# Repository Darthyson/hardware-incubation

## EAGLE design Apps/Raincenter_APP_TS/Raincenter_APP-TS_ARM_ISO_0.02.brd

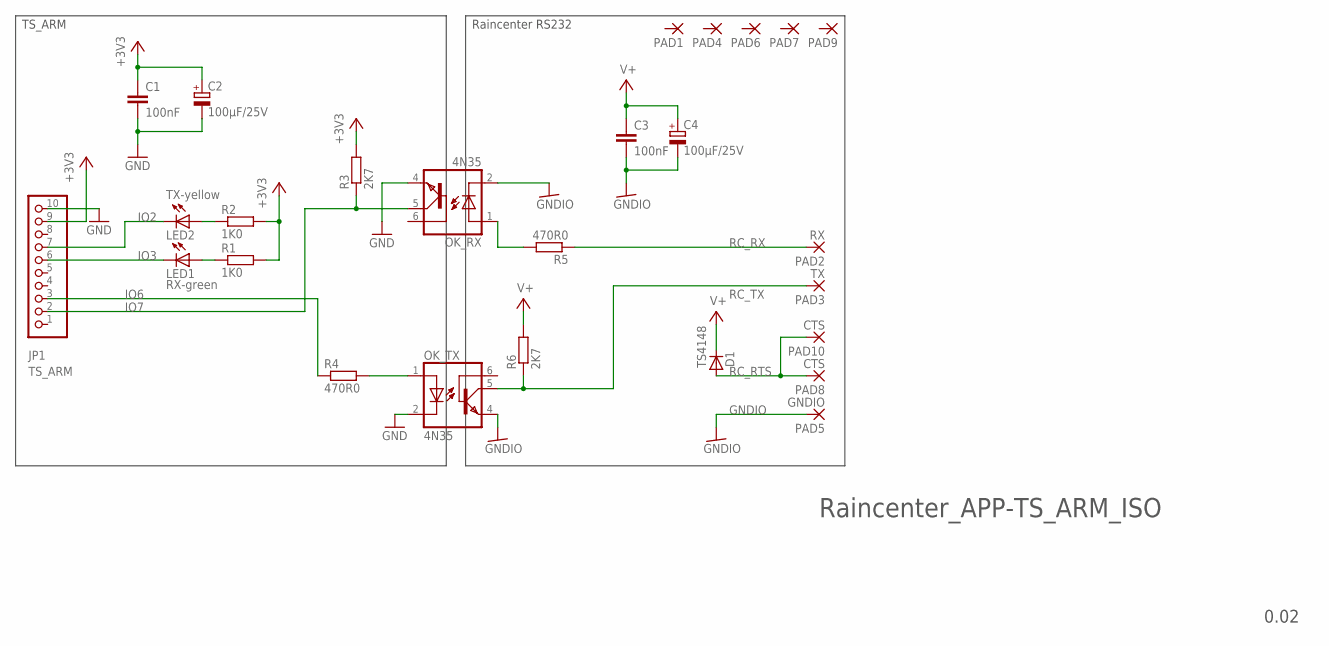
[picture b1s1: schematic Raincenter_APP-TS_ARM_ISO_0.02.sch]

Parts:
C1, C3: 100nF; C1206K
C2, C4: 100µF/25V; PANASONIC_D
D1: TS4148; 1206
JP1: TS_ARM; 1X10
LED1: RX-green; CHIPLED_1206
LED2: TX-yellow; CHIPLED_1206
OK_RX: 4N35; DIL06
OK_TX: 4N35; DIL06
PAD1, PAD4, PAD6, PAD7, PAD9: WIREPADSMD1,27-254; SMD1,27-2,54
PAD2: RX; SMD1,27-2,54
PAD3: TX; SMD1,27-2,54
PAD5: GNDIO; SMD1,27-2,54
PAD8, PAD10: CTS; SMD1,27-2,54
R1, R2: 1K0; R1206
R3, R6: 2K7; R1206
R4, R5: 470R0; R1206

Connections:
+3V3: C1.1, C2.+, JP1.9, R1.2, R2.2, R3.2
GND: C1.2, C2.-, JP1.10, OK_RX.4 (EMI), OK_TX.2 (C)
GNDIO: C3.2, C4.-, OK_RX.2 (C), OK_TX.4 (EMI), PAD5.1
IO2: JP1.7, LED2.C
IO3: JP1.6, LED1.C
IO6: JP1.3, R4.1
IO7: JP1.2, OK_RX.5 (COL), R3.1
unnamed: LED2.A, R2.1
unnamed: OK_RX.1 (A), R5.2
unnamed: OK_TX.1 (A), R4.2
unnamed: LED1.A, R1.1
RC_RTS: D1.ANODE (A), PAD8.1, PAD10.1
RC_RX: PAD2.1, R5.1
RC_TX: OK_TX.5 (COL), PAD3.1, R6.1
V+: C3.1, C4.+, D1.KATHODE (K), R6.2

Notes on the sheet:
Raincenter_APP-TS_ARM_ISO
0.02
Raincenter RS232
TS_ARM

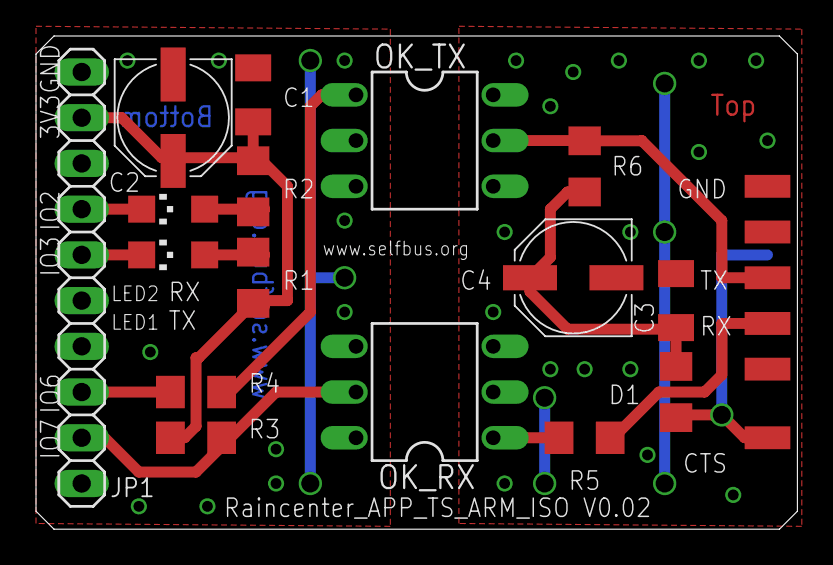
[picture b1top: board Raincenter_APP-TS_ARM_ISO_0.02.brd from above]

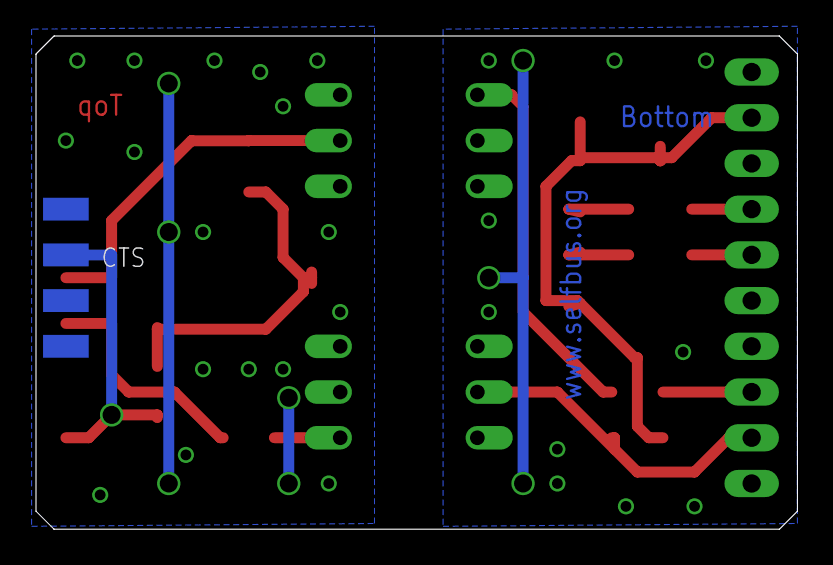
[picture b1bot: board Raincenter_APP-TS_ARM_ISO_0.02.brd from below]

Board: 2 copper layers, 42.3 x 27.4 mm, 26 parts (4 on the bottom side), 15 nets.

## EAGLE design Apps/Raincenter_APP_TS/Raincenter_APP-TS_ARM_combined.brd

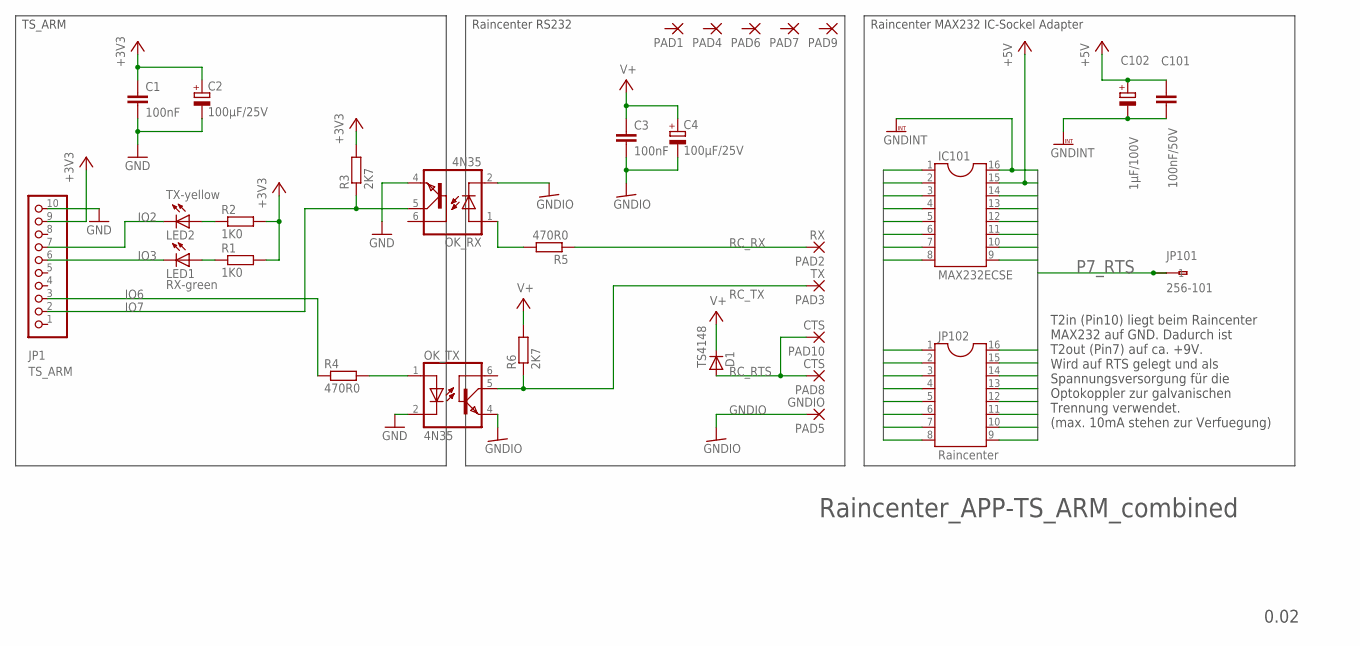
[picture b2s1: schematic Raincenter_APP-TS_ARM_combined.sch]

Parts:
C1, C3: 100nF; C1206K
C2, C4: 100µF/25V; PANASONIC_D
C101: 100nF/50V; C025-024X044
C102: 1µF/100V; E2,5-6
D1: TS4148; 1206
IC101: MAX232ECSE; SOCKET-16
JP1: TS_ARM; 1X10
JP101: 256-101; 255-401-5
JP102: Raincenter; SOCKET-16; MPN AR-16-ST/T
LED1: RX-green; CHIPLED_1206
LED2: TX-yellow; CHIPLED_1206
OK_RX: 4N35; DIL06
OK_TX: 4N35; DIL06
PAD1, PAD4, PAD6, PAD7, PAD9: WIREPADSMD1,27-254; SMD1,27-2,54
PAD2: RX; SMD1,27-2,54
PAD3: TX; SMD1,27-2,54
PAD5: GNDIO; SMD1,27-2,54
PAD8, PAD10: CTS; SMD1,27-2,54
R1, R2: 1K0; R1206
R3, R6: 2K7; R1206
R4, R5: 470R0; R1206

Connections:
+3V3: C1.1, C2.+, JP1.9, R1.2, R2.2, R3.2
+5V: C101.1, C102.+, IC101.15, JP102.2
GND: C1.2, C2.-, JP1.10, OK_RX.4 (EMI), OK_TX.2 (C)
GNDINT: C101.2, C102.-, IC101.16, JP102.1
GNDIO: C3.2, C4.-, OK_RX.2 (C), OK_TX.4 (EMI), PAD5.1
IO2: JP1.7, LED2.C
IO3: JP1.6, LED1.C
IO6: JP1.3, R4.1
IO7: JP1.2, OK_RX.5 (COL), R3.1
unnamed: LED2.A, R2.1
unnamed: OK_RX.1 (A), R5.2
unnamed: OK_TX.1 (A), R4.2
unnamed: LED1.A, R1.1
P1: IC101.1, JP102.16
P2: IC101.2, JP102.15
P3: IC101.3, JP102.14
P4: IC101.4, JP102.13
P5: IC101.5, JP102.12
P6: IC101.6, JP102.11
P7_RTS: IC101.7, JP101.A1 (1), JP101.B1 (2), JP102.10
P8: IC101.8, JP102.9
P9: IC101.9, JP102.8
P10: IC101.10, JP102.7
P11: IC101.11, JP102.6
P12: IC101.12, JP102.5
P13: IC101.13, JP102.4
P14: IC101.14, JP102.3
RC_RTS: D1.ANODE (A), PAD8.1, PAD10.1
RC_RX: PAD2.1, R5.1
RC_TX: OK_TX.5 (COL), PAD3.1, R6.1
V+: C3.1, C4.+, D1.KATHODE (K), R6.2

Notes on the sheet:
Raincenter_APP-TS_ARM_combined
0.02
Raincenter RS232
TS_ARM
Raincenter MAX232 IC-Sockel Adapter
T2in (Pin10) liegt beim Raincenter MAX232 auf GND. Dadurch ist T2out (Pin7) auf ca. +9V. Wird auf RTS gelegt und als Spannungsversorgung für die Optokoppler zur galvanischen Trennung verwendet. (max. 10mA stehen zur Verfuegung)

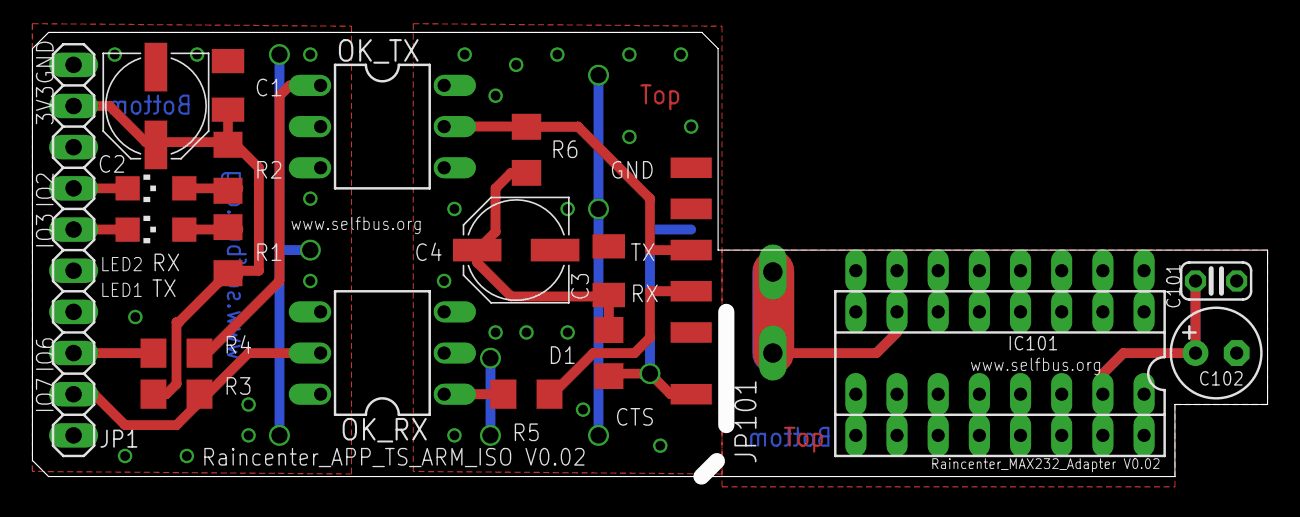
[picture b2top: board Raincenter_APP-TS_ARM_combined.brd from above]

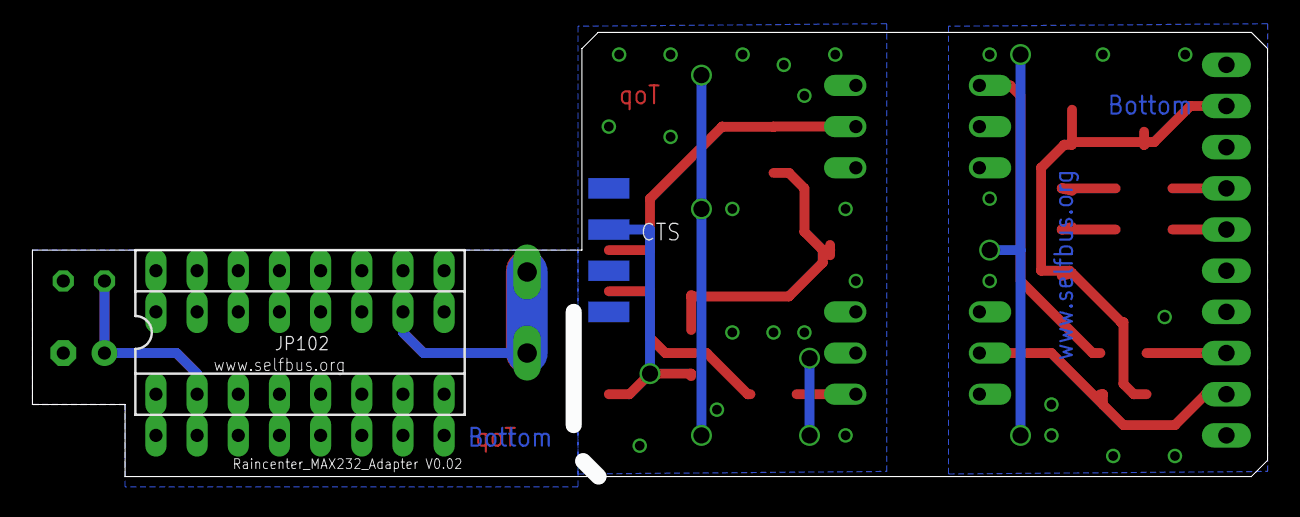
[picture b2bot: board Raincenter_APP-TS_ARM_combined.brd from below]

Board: 2 copper layers, 76.2 x 27.4 mm, 31 parts (5 on the bottom side), 31 nets.

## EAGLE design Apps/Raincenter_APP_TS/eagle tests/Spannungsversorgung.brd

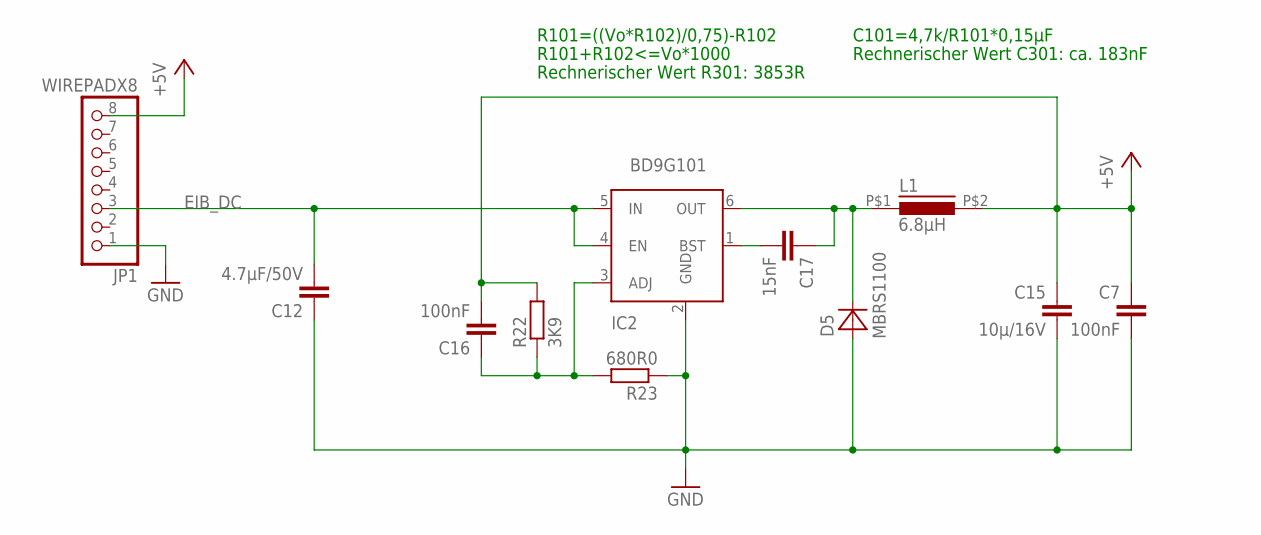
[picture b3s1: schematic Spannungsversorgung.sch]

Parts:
C7, C16: 100nF; C1206
C12: 4.7µF/50V; C1206
C15: 10µ/16V; C1206
C17: 15nF; C1206
D5: MBRS1100; SMA
IC2: BD9G101; SOT23-6; DIGI-KEY BD9G101G-CT-ND
JP1: WIREPADX8; SMD1,27X2,54X8
L1: 6.8µH; PIS2812
R22: 3K9; R1206
R23: 680R0; R1206

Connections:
+5V: C7.1, C15.1, C16.2, JP1.8, L1.P$2 (2), R22.2
EIB_DC: C12.2, IC2.4 (EN), IC2.5 (IN), JP1.3
GND: C7.2, C12.1, C15.2, D5.A, IC2.2 (GND), JP1.1, R23.1
LX1: C17.1, D5.C, IC2.6 (OUT), L1.P$1 (1)
unnamed: C17.2, IC2.1 (BST)
unnamed: C16.1, IC2.3 (ADJ), R22.1, R23.2

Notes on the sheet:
R101=((Vo*R102)/0,75)-R102
R101+R102<=Vo*1000
Rechnerischer Wert R301: 3853R
C101=4,7k/R101*0,15µF
Rechnerischer Wert C301: ca. 183nF

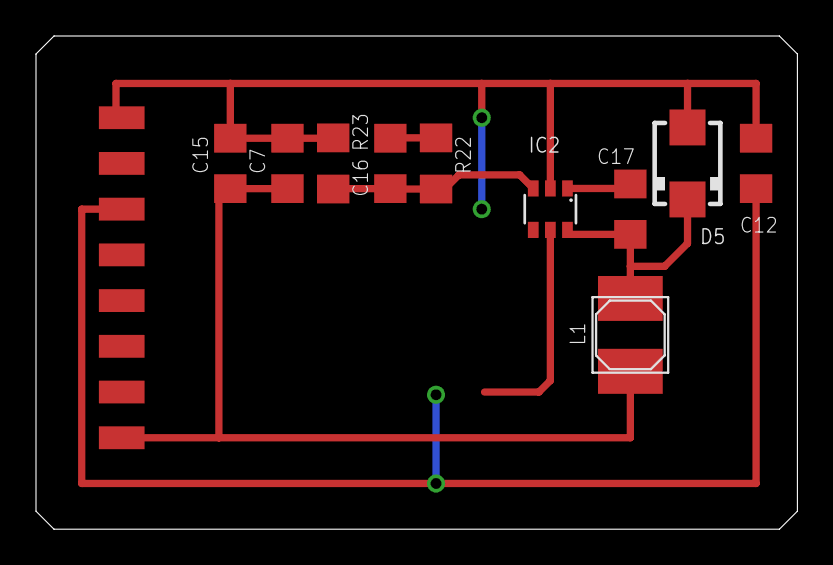
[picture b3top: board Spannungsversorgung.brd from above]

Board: 2 copper layers, 42.3 x 27.4 mm, 11 parts (0 on the bottom side), 6 nets.

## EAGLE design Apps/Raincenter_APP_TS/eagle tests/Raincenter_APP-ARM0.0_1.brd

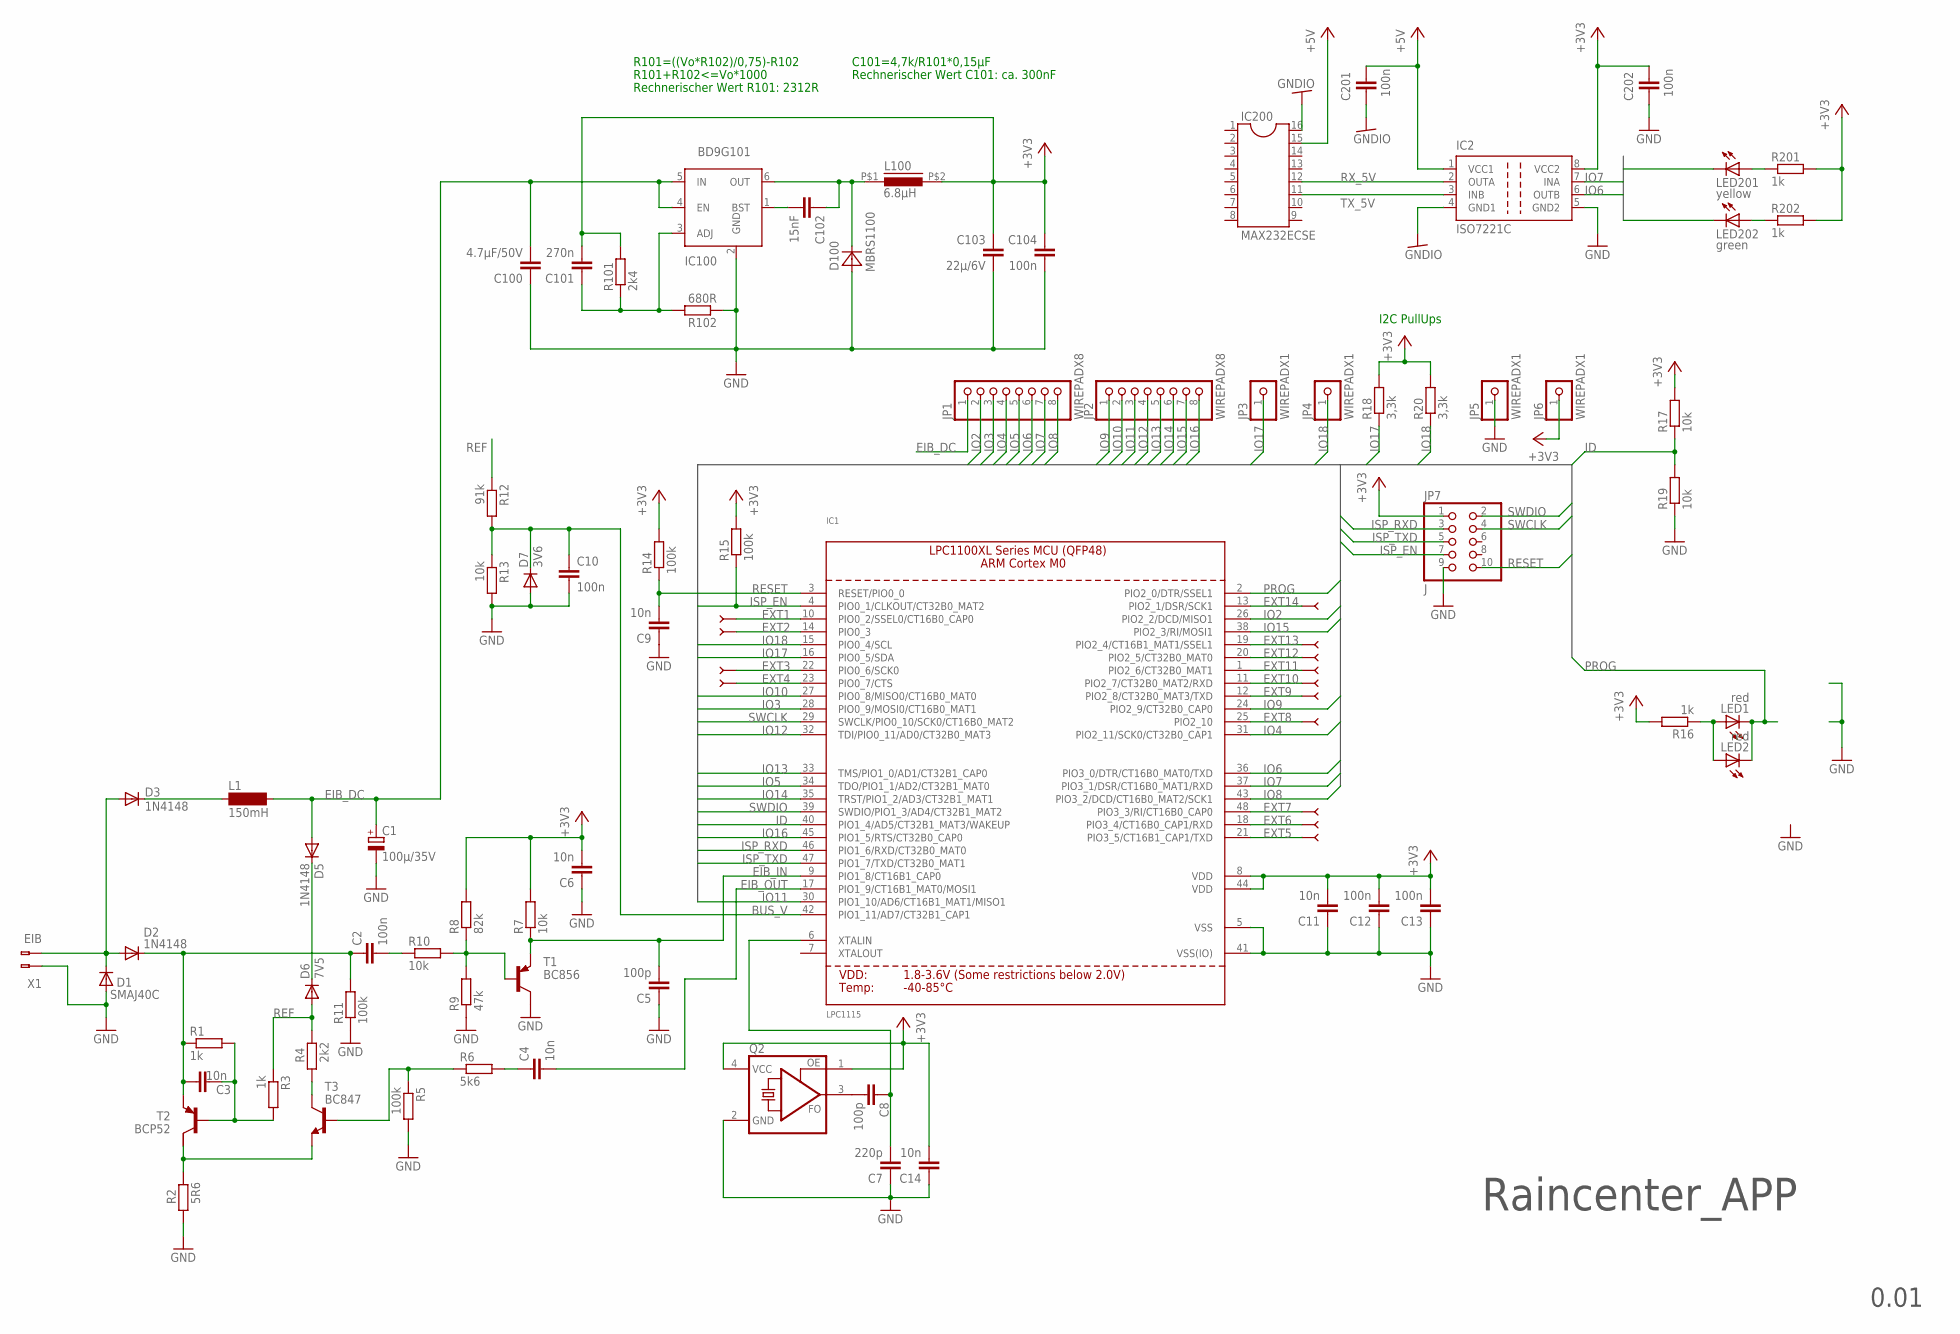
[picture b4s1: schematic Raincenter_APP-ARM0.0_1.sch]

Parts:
C1: 100µ/35V; SANYO-OSCON_SMD_C6
C2, C10, C12, C13, C104, C201, C202: 100n; C1206
C3, C4, C6, C9, C11, C14: 10n; C1206
C5, C8: 100p; C1206
C7: 220p; C1206
C100: 4.7µF/50V; C1206
C101: 270n; C1206
C102: 15nF; C1206
C103: 22µ/6V; C1206
D1: SMAJ40C; SMB
D2, D3, D5: 1N4148; MINIMELF
D6: 7V5; MINIMELF
D7: 3V6; MINIMELF
D100: MBRS1100; SMA
IC1: LPC1115; LQFP48
IC2: ISO7221C; SO-08
IC100: BD9G101; SOT23-6
IC200: MAX232ECSE; SOCKET-16
JP1, JP2: WIREPADX8; SMD1,27X2,54X8
JP3, JP4, JP5, JP6: WIREPADX1; SMD1,27X2,54
JP7: J; 2X05M
L1: 150mH; SD12_1000
L100: 6.8µH; PIS2812
LED1: red; CHIPLED_1206
LED2: red; LED3MM
LED201: yellow; CHIPLED_1206
LED202: green; CHIPLED_1206
P1, P2, P3, P4, P5, P6, P7, P8, P9, P10, P11, P12, P13, P14: PAD
Q2: ASFL; ASF
R1, R3, R16, R201, R202: 1k; R1206
R2: 5R6; R1206
R4: 2k2; R1206
R5, R11, R14, R15: 100k; R1206
R6: 5k6; R1206
R7, R10, R13, R17, R19: 10k; R1206
R8: 82k; R1206
R9: 47k; R1206
R12: 91k; R1206
R18, R20: 3,3k; R1206
R101: 2k4; R1206
R102: 680R; R1206
T1: BC856; SOT23-BEC
T2: BCP52; SOT223
T3: BC847; SOT23
X1: EIB; BUSKLEMME243-724

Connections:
+3V3: C6.2, C11.2, C12.2, C13.2, C14.2, C101.2, C103.1, C104.1, C202.1, IC1.8 (VDD), IC1.44 (VDD), IC2.8 (VCC2), JP6.1, JP7.1, L100.P$2 (2), Q2.1 (OE), Q2.4 (VCC), R7.2, R8.2, R14.2, R15.2, R16.2, R17.2, R18.2, R20.2, R101.2, R201.2, R202.2
+5V: C201.1, IC2.1 (VCC1), IC200.15
BUS_V: C10.2, D7.C, IC1.42 (PIO1_11/AD7/CT32B1_CAP1), R12.2, R13.1
DRAIN: C2.1, C3.1, D2.C, R1.1, R11.2, T2.3 (E)
EIB+: D1.1 (C), D2.A, D3.A, X1.2 (B-2)
EIB_DC: C1.+, C100.2, D5.A, IC100.4 (EN), IC100.5 (IN), JP1.1, L1.2
EIB_IN: C5.2, IC1.9 (PIO1_8/CT16B1_CAP0), R7.1, T1.E
EIB_OUT: C4.2, IC1.17 (PIO1_9/CT16B1_MAT0/MOSI1)
EXT1: IC1.10 (PIO0_2/SSEL0/CT16B0_CAP0), P1.1
EXT2: IC1.14 (PIO0_3), P2.1
EXT3: IC1.22 (PIO0_6/SCK0), P13.1
EXT4: IC1.23 (PIO0_7/CTS), P14.1
EXT5: IC1.21 (PIO3_5/CT16B1_CAP1/TXD), P12.1
EXT6: IC1.18 (PIO3_4/CT16B0_CAP1/RXD), P11.1
EXT7: IC1.48 (PIO3_3/RI/CT16B0_CAP0), P10.1
EXT8: IC1.25 (PIO2_10), P6.1
EXT9: IC1.12 (PIO2_8/CT32B0_MAT3/TXD), P4.1
EXT10: IC1.11 (PIO2_7/CT32B0_MAT2/RXD), P5.1
EXT11: IC1.1 (PIO2_6/CT32B0_MAT1), P9.1
EXT12: IC1.20 (PIO2_5/CT32B0_MAT0), P8.1
EXT13: IC1.19 (PIO2_4/CT16B1_MAT1/SSEL1), P7.1
EXT14: IC1.13 (PIO2_1/DSR/SCK1), P3.1
GND: C1.-, C5.1, C6.1, C7.1, C9.1, C10.1, C11.1, C12.1, C13.1, C14.1, C100.1, C103.2, C104.2, C202.2, D1.2 (A), D7.A, D100.A, IC1.5 (VSS), IC1.41 (VSS(IO)), IC2.5 (GND2), IC100.2 (GND), JP5.1, JP7.9, Q2.2 (GND), R2.1, R5.2, R9.1, R11.1, R13.2, R19.1, R102.1, T1.C, X1.1 (B-1)
GNDIO: C201.2, IC2.4 (GND1), IC200.16
ID: IC1.40 (PIO1_4/AD5/CT32B1_MAT3/WAKEUP), R17.1, R19.2
IO2: IC1.26 (PIO2_2/DCD/MISO1), JP1.2, LED201.C
IO3: IC1.28 (PIO0_9/MOSI0/CT16B0_MAT1), JP1.3, LED202.C
IO4: IC1.31 (PIO2_11/SCK0/CT32B0_CAP1), JP1.4
IO5: IC1.34 (TDO/PIO1_1/AD2/CT32B1_MAT0), JP1.5
IO6: IC1.36 (PIO3_0/DTR/CT16B0_MAT0/TXD), IC2.6 (OUTB), JP1.6
IO7: IC1.37 (PIO3_1/DSR/CT16B0_MAT1/RXD), IC2.7 (INA), JP1.7
IO8: IC1.43 (PIO3_2/DCD/CT16B0_MAT2/SCK1), JP1.8
IO9: IC1.24 (PIO2_9/CT32B0_CAP0), JP2.1
IO10: IC1.27 (PIO0_8/MISO0/CT16B0_MAT0), JP2.2
IO11: IC1.30 (PIO1_10/AD6/CT16B1_MAT1/MISO1), JP2.3
IO12: IC1.32 (TDI/PIO0_11/AD0/CT32B0_MAT3), JP2.4
IO13: IC1.33 (TMS/PIO1_0/AD1/CT32B1_CAP0), JP2.5
IO14: IC1.35 (TRST/PIO1_2/AD3/CT32B1_MAT1), JP2.6
IO15: IC1.38 (PIO2_3/RI/MOSI1), JP2.7
IO16: IC1.45 (PIO1_5/RTS/CT32B0_CAP0), JP2.8
IO17: IC1.16 (PIO0_5/SDA), JP3.1, R18.1
IO18: IC1.15 (PIO0_4/SCL), JP4.1, R20.1
ISP_EN: IC1.4 (PIO0_1/CLKOUT/CT32B0_MAT2), JP7.7, R15.1
ISP_RXD: IC1.46 (PIO1_6/RXD/CT32B0_MAT0), JP7.3
ISP_TXD: IC1.47 (PIO1_7/TXD/CT32B0_MAT1), JP7.5
LX: C102.1, D100.C, IC100.6 (OUT), L100.P$1 (1)
unnamed: C2.2, R10.1
unnamed: C101.1, IC100.3 (ADJ), R101.1, R102.2
unnamed: C4.1, R6.2
unnamed: C7.2, C8.1, IC1.6 (XTALIN)
unnamed: LED201.A, R201.1
unnamed: R4.1, T3.3 (C)
unnamed: R2.2, T2.2 (C), T3.2 (E)
unnamed: D3.C, L1.1
unnamed: D5.C, D6.C
unnamed: C8.2, Q2.3 (FO)
unnamed: LED202.A, R202.1
unnamed: R5.1, R6.1, T3.1 (B)
unnamed: R8.1, R9.2, R10.2, T1.B
unnamed: C3.2, R1.2, R3.2, T2.1 (B)
unnamed: C102.2, IC100.1 (BST)
unnamed: LED1.A, LED2.A, R16.1
PROG: IC1.2 (PIO2_0/DTR/SSEL1), LED1.C, LED2.K (C)
REF: D6.A, R3.1, R4.2, R12.1
RESET: C9.2, IC1.3 (RESET/PIO0_0), JP7.10, R14.1
RX_5V: IC2.2 (OUTA), IC200.12
SWCLK: IC1.29 (SWCLK/PIO0_10/SCK0/CT16B0_MAT2), JP7.4
SWDIO: IC1.39 (SWDIO/PIO1_3/AD4/CT32B1_MAT2), JP7.2
TX_5V: IC2.3 (INB), IC200.11

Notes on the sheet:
R101=((Vo*R102)/0,75)-R102
R101+R102<=Vo*1000
Rechnerischer Wert R101: 2312R
C101=4,7k/R101*0,15µF
Rechnerischer Wert C101: ca. 300nF
I2C PullUps
Raincenter_APP
0.01

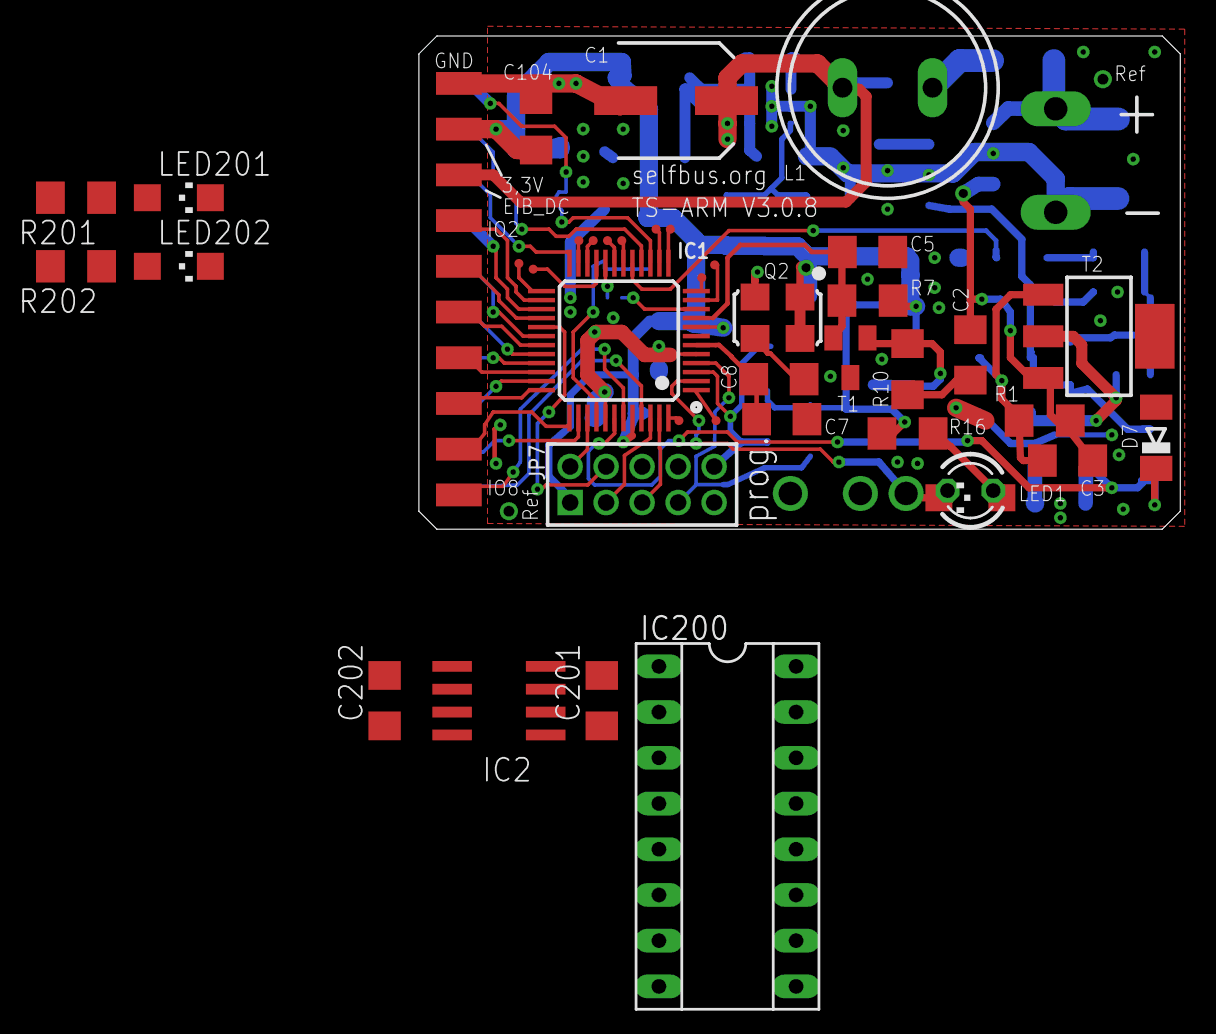
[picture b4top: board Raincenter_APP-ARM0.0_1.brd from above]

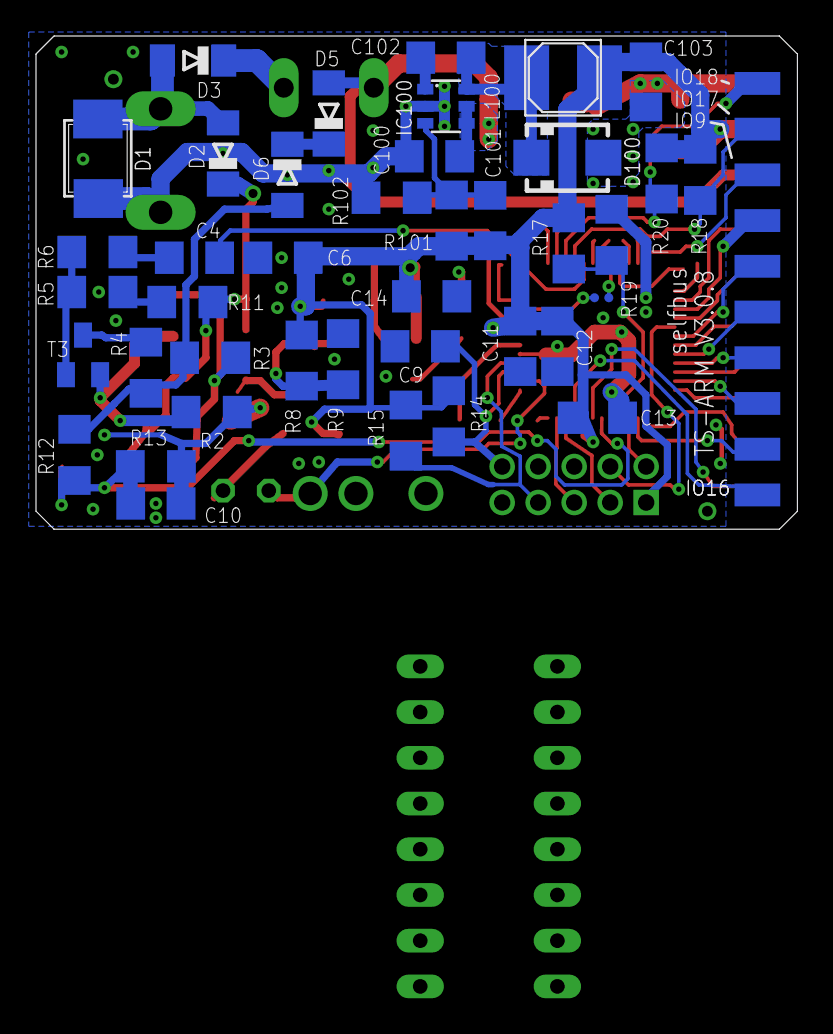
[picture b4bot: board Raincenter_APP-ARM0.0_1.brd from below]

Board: 2 copper layers, 42.3 x 27.4 mm, 88 parts (44 on the bottom side), 69 nets.

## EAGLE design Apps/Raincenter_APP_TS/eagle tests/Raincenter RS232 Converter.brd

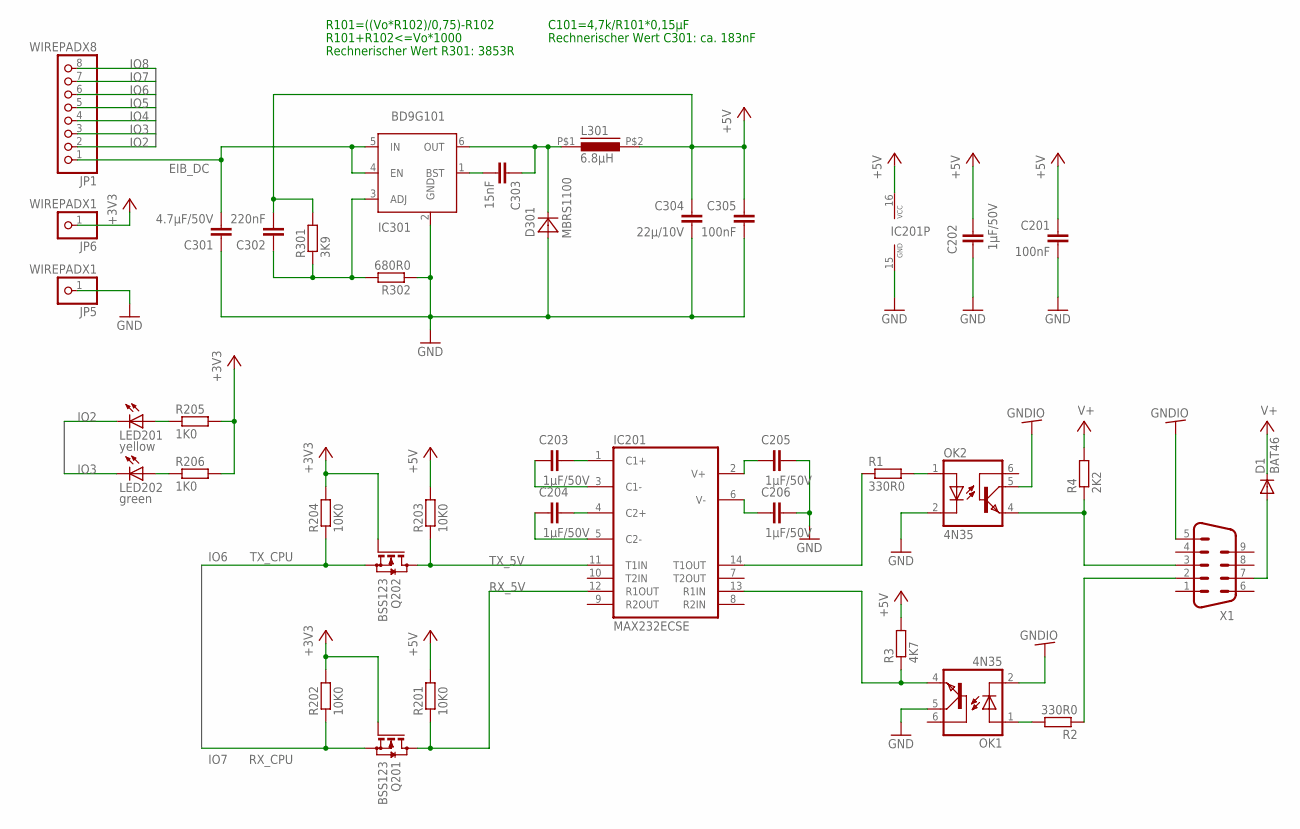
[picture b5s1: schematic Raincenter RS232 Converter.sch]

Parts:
C201, C305: 100nF; C1206
C202, C203, C204, C205, C206: 1µF/50V; C1206
C301: 4.7µF/50V; C1206
C302: 220nF; C1206
C303: 15nF; C1206
C304: 22µ/10V; C1206
D1: BAT46; DO35-7
D301: MBRS1100; SMA
IC201: MAX232ECSE; SO16
IC301: BD9G101; SOT23-6; DIGI-KEY BD9G101G-CT-ND
JP1: WIREPADX8; SMD1,27X2,54X8
JP5, JP6: WIREPADX1; SMD1,27X2,54
L301: 6.8µH; PIS2812
LED201: yellow; CHIPLED_1206
LED202: green; CHIPLED_1206
OK1, OK2: 4N35; DIL06
Q201, Q202: BSS123; SOT23
R1, R2: 330R0; R1206
R3: 4K7; R1206
R4: 2K2; R1206
R201, R202, R203, R204: 10K0; R1206
R205, R206: 1K0; R1206
R301: 3K9; R1206
R302: 680R0; R1206
X1: M09HP

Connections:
+3V3: JP6.1, Q201.1 (G), Q202.1 (G), R202.2, R204.2, R205.2, R206.2
+5V: C201.1, C202.1, C302.2, C304.1, C305.1, IC201.16 (VCC), L301.P$2 (2), R3.2, R201.2, R203.2, R301.2
EIB_DC: C301.2, IC301.4 (EN), IC301.5 (IN), JP1.1
GND: C201.2, C202.2, C205.1, C206.1, C301.1, C304.2, C305.2, D301.A, IC201.15 (GND), IC301.2 (GND), JP5.1, OK1.5 (COL), OK2.2 (C), R302.1
GNDIO: OK1.2 (C), OK2.5 (COL), X1.5
IO2: JP1.2, LED201.C
IO3: JP1.3, LED202.C
IO4: JP1.4
IO5: JP1.5
IO6: JP1.6, Q202.2 (S), R204.1
IO7: JP1.7, Q201.2 (S), R202.1
IO8: JP1.8
LX1: C303.1, D301.C, IC301.6 (OUT), L301.P$1 (1)
unnamed: C303.2, IC301.1 (BST)
unnamed: OK2.4 (EMI), R4.1, X1.3
unnamed: C302.1, IC301.3 (ADJ), R301.1, R302.2
unnamed: R2.1, X1.2
unnamed: LED201.A, R205.1
unnamed: IC201.14 (T1OUT), R1.1
unnamed: D1.A, X1.7
unnamed: OK1.1 (A), R2.2
unnamed: IC201.13 (R1IN), OK1.4 (EMI), R3.1
unnamed: OK2.1 (A), R1.2
unnamed: LED202.A, R206.1
unnamed: C203.1, IC201.1 (C1+)
unnamed: C203.2, IC201.3 (C1-)
unnamed: C205.2, IC201.2 (V+)
unnamed: C206.2, IC201.6 (V-)
unnamed: C204.1, IC201.4 (C2+)
unnamed: C204.2, IC201.5 (C2-)
RX_5V: IC201.12 (R1OUT), Q201.3 (D), R201.1
TX_5V: IC201.11 (T1IN), Q202.3 (D), R203.1
V+: D1.C, R4.2

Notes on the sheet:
R101=((Vo*R102)/0,75)-R102
R101+R102<=Vo*1000
Rechnerischer Wert R301: 3853R
C101=4,7k/R101*0,15µF
Rechnerischer Wert C301: ca. 183nF
RX_CPU
TX_CPU

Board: 2 copper layers, 38 parts (1 on the bottom side), 30 nets, no tracks yet.

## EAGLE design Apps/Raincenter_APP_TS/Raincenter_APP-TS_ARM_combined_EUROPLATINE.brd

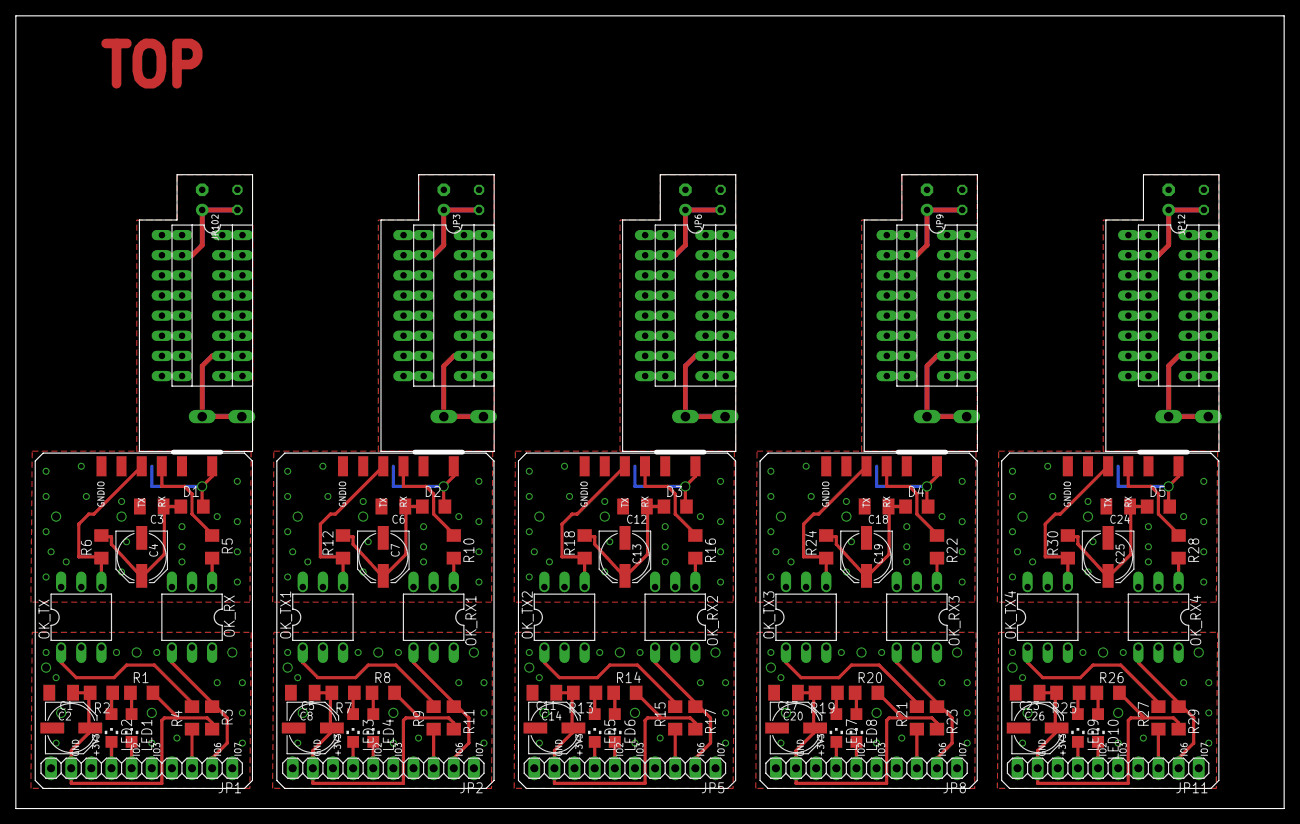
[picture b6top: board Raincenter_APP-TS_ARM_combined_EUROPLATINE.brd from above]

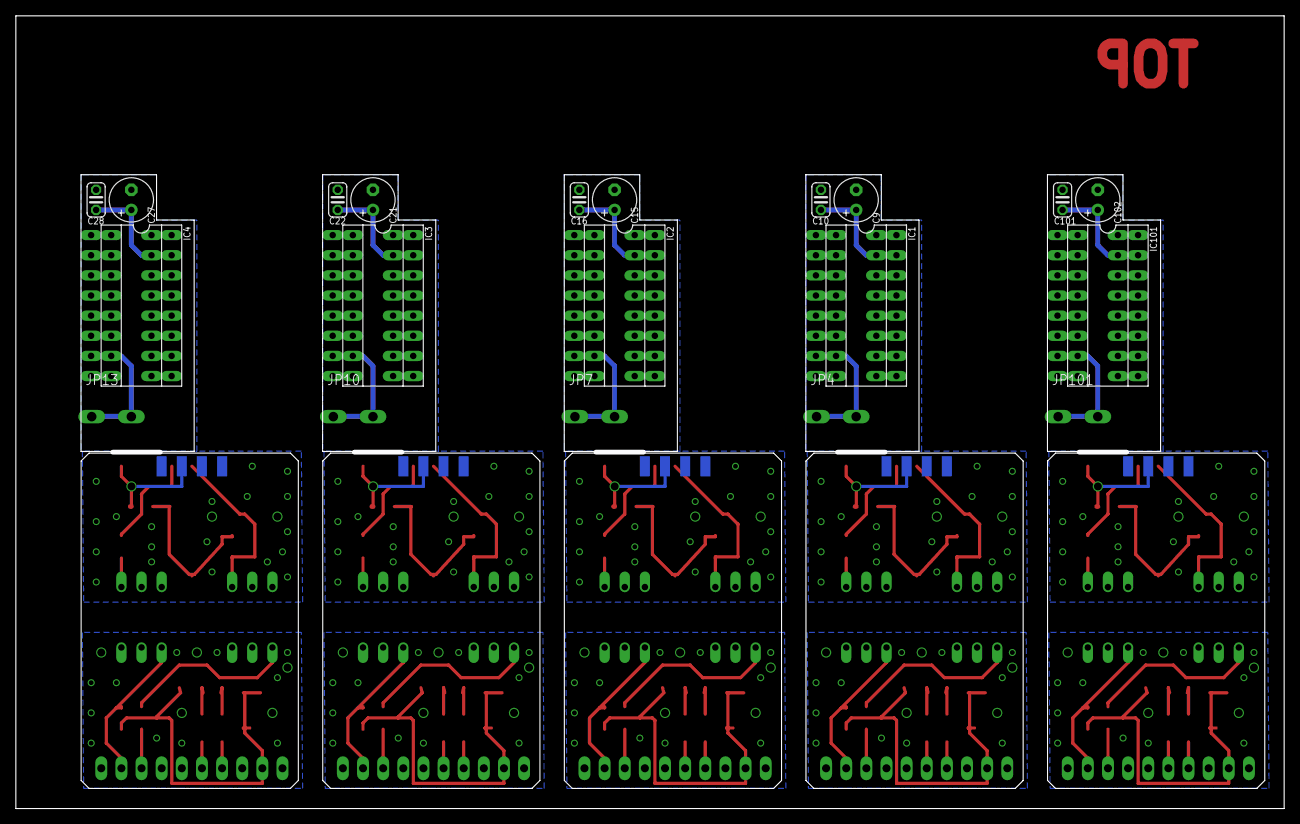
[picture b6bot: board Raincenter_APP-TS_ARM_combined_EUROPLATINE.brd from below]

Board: 2 copper layers, 160.0 x 100.0 mm, 155 parts (40 on the bottom side), 155 nets.

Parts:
C1, C3, C5, C6, C11, C12, C17, C18, C23, C24: 100nF; C1206K
C2, C4, C7, C8, C13, C14, C19, C20, C25, C26: 100µF 25V; PANASONIC_D
C9, C15, C21, C27, C102: 1µF/100V; E2,5-6
C10, C16, C22, C28, C101: 100nF/50V; C025-024X044
D1, D2, D3, D4, D5: TS4148; 1206
IC1, IC2, IC3, IC4, IC101: MAX232ECSE; SOCKET-16
JP1, JP2, JP5, JP8, JP11: TS_ARM; 1X10
JP3, JP6, JP9, JP12, JP102: Raincenter; SOCKET-16
JP4, JP7, JP10, JP13, JP101: 256-101; 255-401-5
LED1, LED4, LED6, LED8, LED10: green; CHIPLED_1206
LED2, LED3, LED5, LED7, LED9: yellow; CHIPLED_1206
OK_RX, OK_RX1, OK_RX2, OK_RX3, OK_RX4: 4N35; DIL06
OK_TX, OK_TX1, OK_TX2, OK_TX3, OK_TX4: 4N35; DIL06
PAD1, PAD4, PAD6, PAD8, PAD9, PAD11, PAD14, PAD16, PAD18, PAD19, PAD21, PAD24, PAD26, PAD28, PAD29, PAD31, PAD34, PAD36, PAD38, PAD39, PAD41, PAD44, PAD46, PAD48, PAD49: SMD1,27-2,54
PAD2, PAD12, PAD22, PAD32, PAD42: RX; SMD1,27-2,54
PAD3, PAD13, PAD23, PAD33, PAD43: TX; SMD1,27-2,54
PAD5, PAD15, PAD25, PAD35, PAD45: GNDIO; SMD1,27-2,54
PAD7, PAD10, PAD17, PAD20, PAD27, PAD30, PAD37, PAD40, PAD47, PAD50: RTS; SMD1,27-2,54
R1, R2, R7, R8, R13, R14, R19, R20, R25, R26: 1K0; R1206
R3, R11, R17, R23, R29: 4K7; R1206
R4, R5, R9, R10, R15, R16, R21, R22, R27, R28: 470R0; R1206
R6, R12, R18, R24, R30: 2K2; R1206

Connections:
+3V1: C5.1, C8.+, JP2.9, R7.2, R8.2, R11.2
+3V2: C11.1, C14.+, JP5.9, R13.2, R14.2, R17.2
+3V3: C1.1, C2.+, JP1.9, R1.2, R2.2, R3.2
+3V4: C17.1, C20.+, JP8.9, R19.2, R20.2, R23.2
+3V5: C23.1, C26.+, JP11.9, R25.2, R26.2, R29.2
+5V: C101.1, C102.+, IC101.15, JP102.2
+5V1: C9.+, C10.1, IC1.15, JP3.2
+5V2: C15.+, C16.1, IC2.15, JP6.2
+5V3: C21.+, C22.1, IC3.15, JP9.2
+5V4: C27.+, C28.1, IC4.15, JP12.2
GND: C1.2, C2.-, JP1.10, OK_RX.5, OK_TX.2
GND1: C5.2, C8.-, JP2.10, OK_RX1.5, OK_TX1.2
GND2: C11.2, C14.-, JP5.10, OK_RX2.5, OK_TX2.2
GND3: C17.2, C20.-, JP8.10, OK_RX3.5, OK_TX3.2
GND4: C23.2, C26.-, JP11.10, OK_RX4.5, OK_TX4.2
GNDINT: C101.2, C102.-, IC101.16, JP102.1
GNDINT1: C9.-, C10.2, IC1.16, JP3.1
GNDINT2: C15.-, C16.2, IC2.16, JP6.1
GNDINT3: C21.-, C22.2, IC3.16, JP9.1
GNDINT4: C27.-, C28.2, IC4.16, JP12.1
GNDIO: C3.2, C4.-, OK_RX.2, OK_TX.5, PAD5.1
GNDIO1: C6.2, C7.-, OK_RX1.2, OK_TX1.5, PAD15.1
GNDIO2: C12.2, C13.-, OK_RX2.2, OK_TX2.5, PAD25.1
GNDIO3: C18.2, C19.-, OK_RX3.2, OK_TX3.5, PAD35.1
GNDIO4: C24.2, C25.-, OK_RX4.2, OK_TX4.5, PAD45.1
IO1: JP2.7, LED3.C
IO2: JP1.7, LED2.C
IO3: JP1.6, LED1.C
IO4: JP2.6, LED4.C
IO5: JP2.3, R9.1
IO6: JP1.3, R4.1
IO7: JP1.2, OK_RX.4, R3.1
IO8: JP2.2, OK_RX1.4, R11.1
IO9: JP5.7, LED5.C
IO10: JP5.6, LED6.C
IO11: JP5.3, R15.1
IO12: JP5.2, OK_RX2.4, R17.1
IO13: JP8.7, LED7.C
IO14: JP8.6, LED8.C
IO15: JP8.3, R21.1
IO16: JP8.2, OK_RX3.4, R23.1
IO17: JP11.7, LED9.C
IO18: JP11.6, LED10.C
IO19: JP11.3, R27.1
IO20: JP11.2, OK_RX4.4, R29.1
unnamed: LED3.A, R7.1
unnamed: LED4.A, R8.1
unnamed: OK_RX1.1, R10.2
unnamed: OK_TX1.1, R9.2
unnamed: LED2.A, R2.1
unnamed: LED5.A, R13.1
unnamed: LED6.A, R14.1
unnamed: OK_RX.1, R5.2
unnamed: OK_RX2.1, R16.2
unnamed: OK_TX.1, R4.2
unnamed: LED1.A, R1.1
unnamed: OK_TX2.1, R15.2
unnamed: LED7.A, R19.1
unnamed: LED8.A, R20.1
unnamed: OK_RX3.1, R22.2
unnamed: OK_TX3.1, R21.2
unnamed: LED9.A, R25.1
unnamed: LED10.A, R26.1
unnamed: OK_RX4.1, R28.2
unnamed: OK_TX4.1, R27.2
P1: IC101.1, JP102.16
P2: IC101.2, JP102.15
P3: IC101.3, JP102.14
P4: IC101.4, JP102.13
P5: IC101.5, JP102.12
P6: IC101.6, JP102.11
P7: IC1.1, JP3.16
P7_RTS: IC101.7, JP101.A1, JP101.B1, JP102.10
P7_RTS1: IC1.7, JP3.10, JP4.A1, JP4.B1
P7_RTS2: IC2.7, JP6.10, JP7.A1, JP7.B1
P7_RTS3: IC3.7, JP9.10, JP10.A1, JP10.B1
P7_RTS4: IC4.7, JP12.10, JP13.A1, JP13.B1
P8: IC101.8, JP102.9
P9: IC101.9, JP102.8
P10: IC101.10, JP102.7
P11: IC101.11, JP102.6
P12: IC101.12, JP102.5
P13: IC101.13, JP102.4
P14: IC101.14, JP102.3
P15: IC1.2, JP3.15
P16: IC1.3, JP3.14
P17: IC1.4, JP3.13
P18: IC1.5, JP3.12
P19: IC1.6, JP3.11
P20: IC1.8, JP3.9
P21: IC1.9, JP3.8
P22: IC1.10, JP3.7
P23: IC1.11, JP3.6
P24: IC1.12, JP3.5
P25: IC1.13, JP3.4
P26: IC1.14, JP3.3
P27: IC2.1, JP6.16
P28: IC2.2, JP6.15
P29: IC2.3, JP6.14
P30: IC2.4, JP6.13
P31: IC2.5, JP6.12
P32: IC2.6, JP6.11
P33: IC2.8, JP6.9
P34: IC2.9, JP6.8
P35: IC2.10, JP6.7
P36: IC2.11, JP6.6
P37: IC2.12, JP6.5
P38: IC2.13, JP6.4
P39: IC2.14, JP6.3
P40: IC3.1, JP9.16
P41: IC3.2, JP9.15
P42: IC3.3, JP9.14
P43: IC3.4, JP9.13
P44: IC3.5, JP9.12
P45: IC3.6, JP9.11
P46: IC3.8, JP9.9
P47: IC3.9, JP9.8
P48: IC3.10, JP9.7
P49: IC3.11, JP9.6
P50: IC3.12, JP9.5
P51: IC3.13, JP9.4
P52: IC3.14, JP9.3
P53: IC4.1, JP12.16
P54: IC4.2, JP12.15
P55: IC4.3, JP12.14
P56: IC4.4, JP12.13
P57: IC4.5, JP12.12
P58: IC4.6, JP12.11
P59: IC4.8, JP12.9
P60: IC4.9, JP12.8
P61: IC4.10, JP12.7
P62: IC4.11, JP12.6
P63: IC4.12, JP12.5
P64: IC4.13, JP12.4
P65: IC4.14, JP12.3
RC_RTS: D1.ANODE, PAD7.1, PAD10.1
RC_RTS1: D2.ANODE, PAD17.1, PAD20.1
RC_RTS2: D3.ANODE, PAD27.1, PAD30.1
RC_RTS3: D4.ANODE, PAD37.1, PAD40.1
RC_RTS4: D5.ANODE, PAD47.1, PAD50.1
RC_RX: PAD2.1, R5.1
RC_RX1: PAD12.1, R10.1
RC_RX2: PAD22.1, R16.1
RC_RX3: PAD32.1, R22.1
RC_RX4: PAD42.1, R28.1
RX_TX: OK_TX.4, PAD3.1, R6.1
RX_TX1: OK_TX1.4, PAD13.1, R12.1
RX_TX2: OK_TX2.4, PAD23.1, R18.1
RX_TX3: OK_TX3.4, PAD33.1, R24.1
RX_TX4: OK_TX4.4, PAD43.1, R30.1
V+: C3.1, C4.+, D1.KATHODE, R6.2
V+1: C6.1, C7.+, D2.KATHODE, R12.2
V+2: C12.1, C13.+, D3.KATHODE, R18.2
V+3: C18.1, C19.+, D4.KATHODE, R24.2
V+4: C24.1, C25.+, D5.KATHODE, R30.2

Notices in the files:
parts and their libraries:
microbuilder: This work is placed in the public domain, and may be freely used for commercial and non-commercial work with the following conditions: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
